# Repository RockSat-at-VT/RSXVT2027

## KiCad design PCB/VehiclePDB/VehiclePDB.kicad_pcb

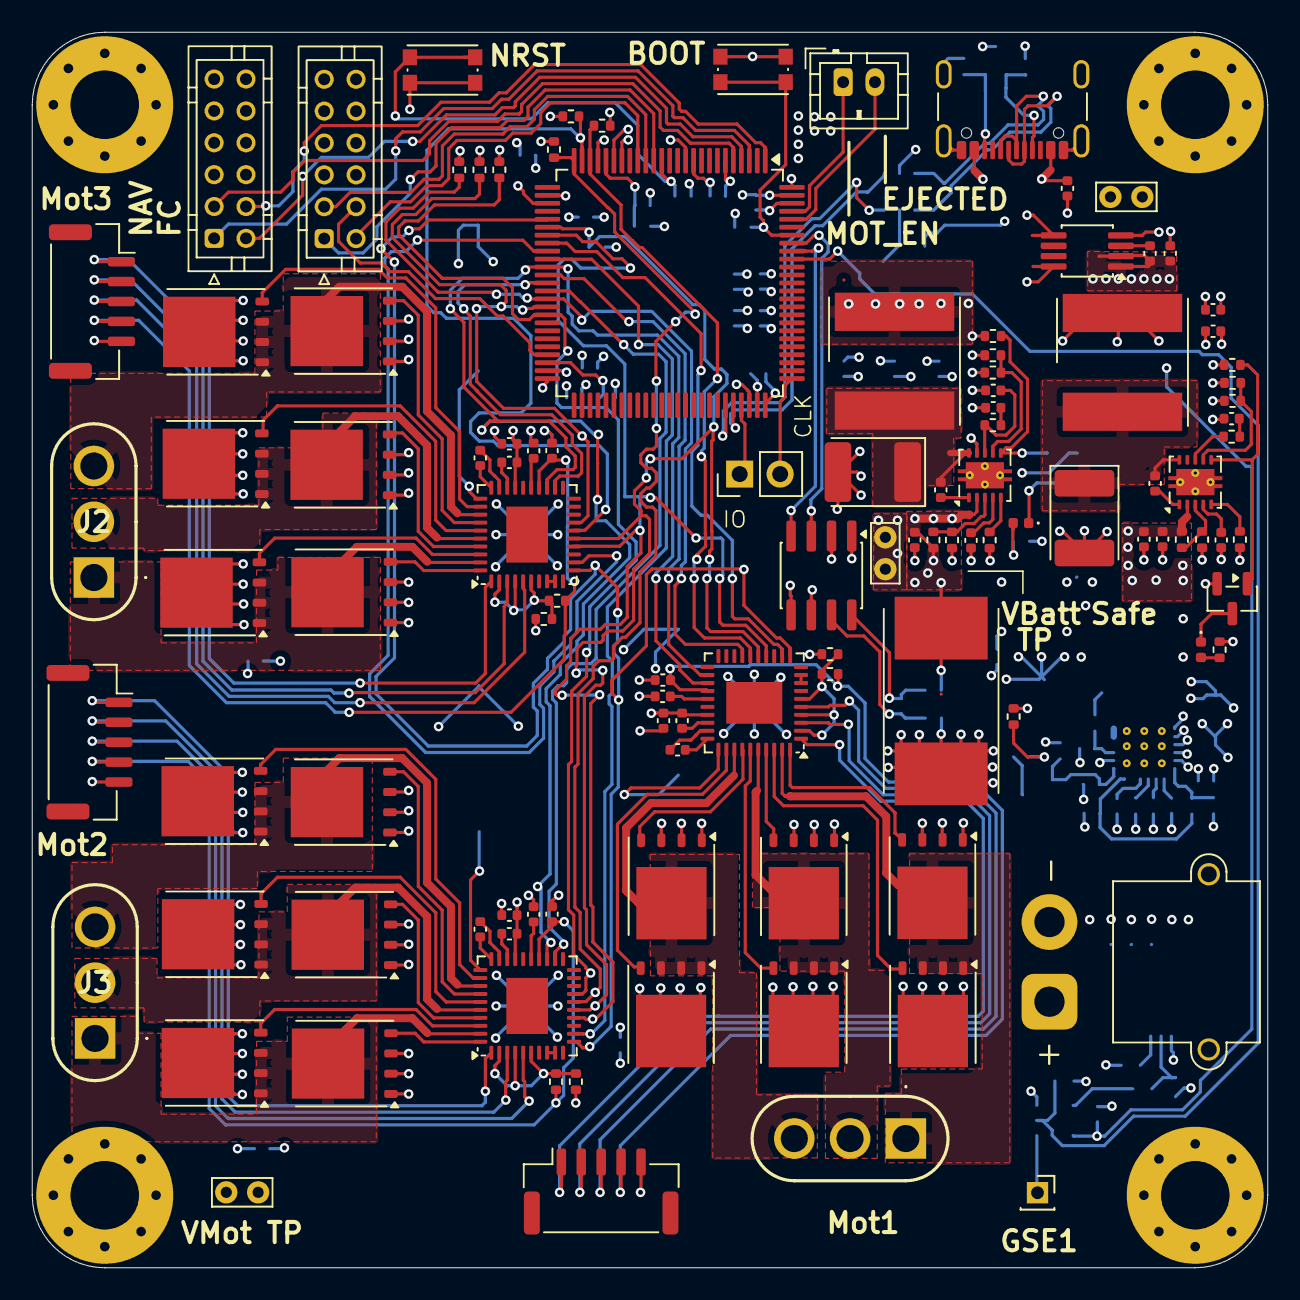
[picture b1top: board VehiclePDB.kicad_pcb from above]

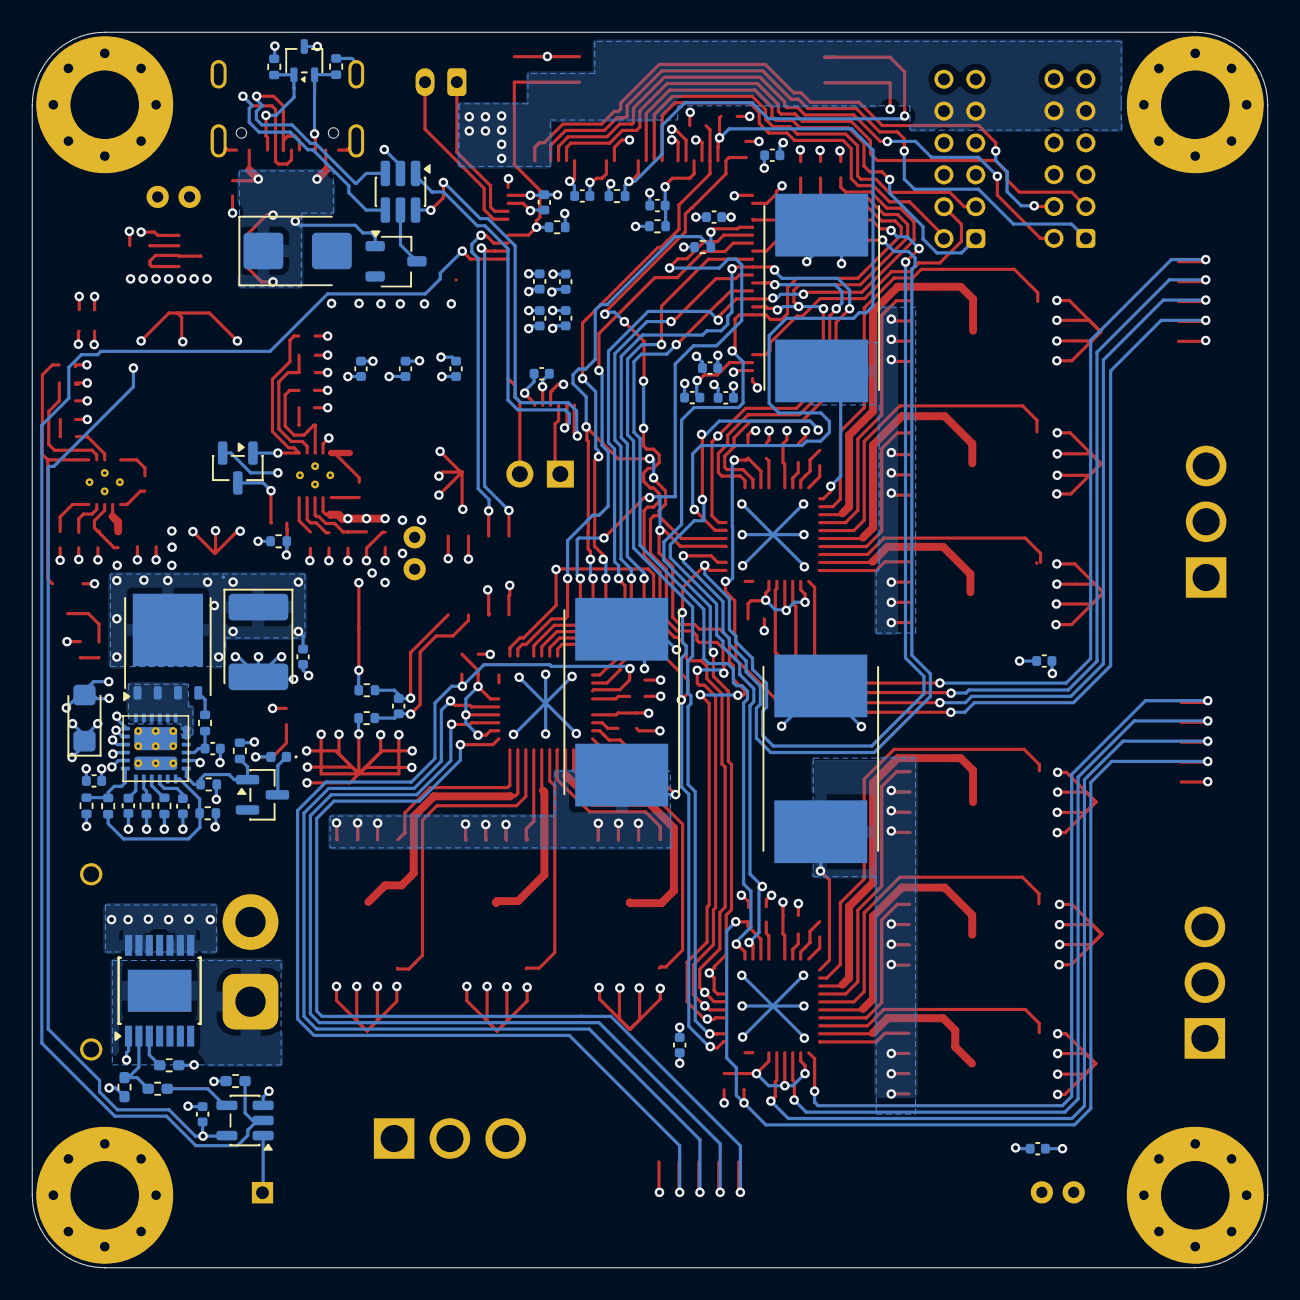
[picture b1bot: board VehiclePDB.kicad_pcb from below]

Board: 4 copper layers, 77.6 x 77.5 mm, 173 parts (63 on the bottom side), 151 nets.

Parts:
C1: 6.8p; C_0402_1005Metric
C2, C3, C16: 100u; C_0402_1005Metric
C4, C6, C32: .01u; C_0402_1005Metric
C5: 4.7n; C_0402_1005Metric
C7, C23, C25, C31, C35, C41, C45, C53, C57: 1u; C_0402_1005Metric
C8: 2.2n; C_0402_1005Metric
C9: 4.3n; C_0402_1005Metric
C10: 8.2n; C_0402_1005Metric
C11: 400u; C_0402_1005Metric
C12: 6.8u; C_0402_1005Metric
C13: 1.2n; C_0402_1005Metric
C14, C15, C28, C29: 2.2u; C_0402_1005Metric
C17, C33: 10u; C_0402_1005Metric
C18, C21, C22, C24, C26, C40, C43, C44, C52, C55, C56: .1u; C_0402_1005Metric
C19, C20: 47u; C_0402_1005Metric
C27, C42, C54: 470u; C_0402_1005Metric
C30, C34, C36, C37, C38, C39, C46, C47, C48, C50: 100n; C_0402_1005Metric
C49: 4.7u; C_0402_1005Metric
D1, D2, D4: SD2114S040S8R0; D_2114_3652Metric
D3, D6, D7: LED; LED_0402_1005Metric
D5: SMF15A; D_SMF
D10: SMBJ6.0A-E3/52; D_SMB
D11: BAT54; TSOT-23
J2, J3: Bullet Conector; MR30PBFB
J4: Conn_01x02_Pin; PinHeader_1x02_P2.54mm_Vertical
J5: USB_C_Receptacle_USB2.0_14P; USB_C_Receptacle_GCT_USB4105-xx-A_16P_TopMnt_Horizontal
J6: Hall1; JST_GH_SM05B-GHS-TB_1x05-1MP_P1.25mm_Horizontal
J7: Hall2; JST_GH_SM05B-GHS-TB_1x05-1MP_P1.25mm_Horizontal
J8: Hall3; JST_GH_SM05B-GHS-TB_1x05-1MP_P1.25mm_Horizontal
J9: battery connector; AMASS_XT30PW-M_1x02_P2.50mm_Horizontal
J10, J11: Conn_02x06_Odd_Even; JST_PHD_B12B-PHDSS_2x06_P2.00mm_Vertical
J12: Conn_01x01_Socket; PinSocket_1x01_P2.00mm_Vertical
J13: Conn_01x02_Pin; JST_PH_B2B-PH-K_1x02_P2.00mm_Vertical
L1: 15u; L_Wurth_WE-LQS-8040
L2: 10u; L_Wurth_WE-LQS-8040
Mot1: Bullet Conector; MR30PBFB
Q1, Q6, Q7, Q8, Q9, Q10, Q11, Q12, Q13, Q14, Q15, Q16, Q17, Q18, Q19, Q20, Q21, Q22: BSC052N08NS5; TDSON-8-1
Q5: BSC026N08NS5; TDSON-8-1
Q23, Q24, Q25: 2N7002; SOT-23
R1, R6: 20k; R_0402_1005Metric
R2, R5, R18, R22, R23, R24, R39, R42, R46: 10k; R_0402_1005Metric
R3: 412k; R_0402_1005Metric
R4: 31.6k; R_0402_1005Metric
R7: 500k; R_0402_1005Metric
R8: 14k; R_0402_1005Metric
R9: 50k; R_0402_1005Metric
R10: 226; R_0402_1005Metric
R11: 5m; R_Shunt_Vishay_WSR2_WSR3
R12: 1.24k; R_0402_1005Metric
R13: 365k; R_0402_1005Metric
R14: 124k; R_0402_1005Metric
R15: 30.1k; R_0402_1005Metric
R16, R19: 105k; R_0402_1005Metric
R17: 15.4k; R_0402_1005Metric
R20, R26, R27, R28, R29, R30, R31, R32, R33, R34, R35, R36, R37, R44: 4.7k; R_0402_1005Metric
R21: 52.3; R_0402_1005Metric
R25, R43, R58: 30m; R_Shunt_Vishay_WSR2_WSR3
R38: 47; R_0402_1005Metric
R40, R41: 5.1k; R_0402_1005Metric
R45: 10k; R_0402_1005Metric_Pad0.72x0.64mm_HandSolder
R47: 2; R_0402_1005Metric
R49, R50, R51: 4.7k; R_0402_1005Metric_Pad0.72x0.64mm_HandSolder
R52, R53: 10; R_0402_1005Metric
SW1, SW2: SW_Push; SW_Push_1P1T_NO_CK_KMR2
TP1, TP1#2, TP2: TestPoint; TestPoint_Bridge_Pitch2.0mm_Drill0.7mm
U1: STM32H523VCTx; LQFP-100_14x14mm_P0.5mm
U2: 74LVC1G32; SOT-23-5
U3, U4: TPS54240DRC; Texas_DRC0010J_ThermalVias
U5, U17, U19: DRV8308; Texas_RHA0040E_VQFN-40-1EP_6x6mm_P0.5mm_EP3.52x2.62mm
U6: TPS25983
U7: BTS7004-1EPP; Infineon_PG-TSDSO-14-22
U9: INA219AxD; SOIC-8_3.9x4.9mm_P1.27mm
U11: IP4234CZ6; SC-74-6_1.55x2.9mm_P0.95mm
U13: TPD2E2U06DCK; SOT-323_SC-70
U14: LT1762-3.3; MSOP-8_3x3mm_P0.65mm

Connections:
3V3: C19.2, C20.2, C30.1, C32.1, C33.1, C34.2, C35.2, C37.1, C38.1, C39.1, C46.1, C47.1, C48.1, C49.1, C50.1, J10.7, J10.8, J11.7, J11.8, J12.1 (Pin_1_1), L2.2, R4.1, R18.2, R28.1, R30.1, R32.1, R34.2, R35.2, R36.2, R37.2, R38.2, R39.1, SW2.1, U1.6 (VBAT), U1.11 (VDD), U1.22 (VDDA), U1.28 (VDD), U1.50 (VDD), U1.73 (VDDUSB), U1.75 (VDD), U1.100 (VDD), U2.1, U2.5 (VCC), U9.5 (VS), U14.1 (OUT), U14.2 (SENSE)
5V: C2.1, C3.1, C16.1, J10.9, J10.10, J11.9, J11.10, L1.2, R21.1, R46.2
/Batt Togle/IS_Ejected: R45.1, U1.91 (PB5), U2.2
/FC2PDB.CLK: J10.4, U1.47 (SPI2_SCK)
/FC2PDB.CS: J10.1, U1.15 (PC0)
/FC2PDB.MISO: J10.2, U1.17 (SPI2_MISO)
/FC2PDB.MOSI: J10.3, U1.16 (SPI2_MOSI)
/Motor Controler MCU/CurrInfo.SCL: U1.92 (I2C1_SCL), U9.4 (SCL)
/Motor Controler MCU/CurrInfo.SDA: U1.93 (I2C1_SDA), U9.3 (SDA)
/Motor Controler MCU/IS_EJECTED: J13.2, U1.96 (PB9)
/Motor Controler MCU/MOTOR_OFF: J13.1, U1.97 (PE0)
/Motor Controler MCU/PDB.CLK: J4.2, U1.76 (DEBUG_JTCK-SWCLK)
/Motor Controler MCU/PDB.IO: J4.1, U1.72 (DEBUG_JTMS-SWDIO)
/Motor Driver One/Motor1.ENABLE: U1.37 (PB2), U5.22 (ENABLE)
/Motor Driver One/Motor1.FAULTn: R37.1, U1.40 (PE9), U5.17 (~FAULTn)
/Motor Driver One/Motor1.FGOUT: R28.2, U1.23 (TIM2_CH1), U5.16 (FGOUT)
/Motor Driver One/Motor1.SPI_CS: U1.33 (PC4), U5.12 (SCS)
/Motor Driver One/Motors_Low: Q6.1 (S), Q6.2 (S), Q6.3 (S), Q7.1 (S), Q7.2 (S), Q7.3 (S), Q9.1 (S), Q9.2 (S), Q9.3 (S), R25.1, U5.31 (ISEN)
/Motor Driver One/U.High: Q1.4 (G), U5.32 (UHSG)
/Motor Driver One/U.Low: Q6.4 (G), U5.34 (ULSG)
/Motor Driver One/U.Switch: Mot1.3, Q1.1 (S), Q1.2 (S), Q1.3 (S), Q6.5 (D), U5.33 (U)
/Motor Driver One/UP: J6.1, U5.1 (UHP)
/Motor Driver One/V.High: Q8.4 (G), U5.35 (VHSG)
/Motor Driver One/V.Low: Q7.4 (G), U5.37 (VLSG)
/Motor Driver One/V.Switch: Mot1.2, Q7.5 (D), Q8.1 (S), Q8.2 (S), Q8.3 (S), U5.36 (V)
/Motor Driver One/VP: J6.2, U5.3 (VHP)
/Motor Driver One/VREG: C24.2, J6.4, R26.1, U5.24 (VREG)
/Motor Driver One/W.High: Q10.4 (G), U5.38 (WHSG)
/Motor Driver One/W.Low: Q9.4 (G), U5.40 (WLSG)
/Motor Driver One/W.Switch: Mot1.1, Q9.5 (D), Q10.1 (S), Q10.2 (S), Q10.3 (S), U5.39 (W)
/Motor Driver One/WP: J6.3, U5.5 (WHP)
/Motor Driver Three/Motor3.ENABLE: U1.39 (PE8), U19.22 (ENABLE)
/Motor Driver Three/Motor3.FAULTn: R35.1, U1.42 (PE11), U19.17 (~FAULTn)
/Motor Driver Three/Motor3.FGOUT: R32.2, U1.25 (TIM2_CH3), U19.16 (FGOUT)
/Motor Driver Three/Motor3.RESET: U1.36 (PB1), U5.23 (RESET), U17.23 (RESET), U19.23 (RESET)
/Motor Driver Three/Motor3.SPI_CLK: U1.30 (SPI1_SCK), U5.11 (SCLK), U17.11 (SCLK), U19.11 (SCLK)
/Motor Driver Three/Motor3.SPI_CS: U1.35 (PB0), U19.12 (SCS)
/Motor Driver Three/Motor3.SPI_MISO: R34.1, U1.31 (SPI1_MISO), U5.15 (SDATAO), U17.15 (SDATAO), U19.15 (SDATAO)
/Motor Driver Three/Motor3.SPI_MOSI: U1.32 (SPI1_MOSI), U5.14 (SDATAI), U17.14 (SDATAI), U19.14 (SDATAI)
/Motor Driver Three/Motors_Low: Q18.1 (S), Q18.2 (S), Q18.3 (S), Q20.1 (S), Q20.2 (S), Q20.3 (S), Q22.1 (S), Q22.2 (S), Q22.3 (S), R58.1, U19.31 (ISEN)
/Motor Driver Three/U.High: Q17.4 (G), U19.32 (UHSG)
/Motor Driver Three/U.Low: Q18.4 (G), U19.34 (ULSG)
/Motor Driver Three/U.Switch: J3.3, Q17.1 (S), Q17.2 (S), Q17.3 (S), Q18.5 (D), U19.33 (U)
/Motor Driver Three/UP: J8.1, U19.1 (UHP)
/Motor Driver Three/V.High: Q19.4 (G), U19.35 (VHSG)
/Motor Driver Three/V.Low: Q20.4 (G), U19.37 (VLSG)
/Motor Driver Three/V.Switch: J3.2, Q19.1 (S), Q19.2 (S), Q19.3 (S), Q20.5 (D), U19.36 (V)
/Motor Driver Three/VP: J8.2, U19.3 (VHP)
/Motor Driver Three/VREG: C56.2, J8.4, R44.1, U19.24 (VREG)
/Motor Driver Three/W.High: Q21.4 (G), U19.38 (WHSG)
/Motor Driver Three/W.Low: Q22.4 (G), U19.40 (WLSG)
/Motor Driver Three/W.Switch: J3.1, Q21.1 (S), Q21.2 (S), Q21.3 (S), Q22.5 (D), U19.39 (W)
/Motor Driver Three/WP: J8.3, U19.5 (WHP)
/Motor Driver Two/Motor2.ENABLE: U1.38 (PE7), U17.22 (ENABLE)
/Motor Driver Two/Motor2.FAULTn: R36.1, U1.41 (PE10), U17.17 (~FAULTn)
/Motor Driver Two/Motor2.FGOUT: R30.2, U1.24 (TIM2_CH2), U17.16 (FGOUT)
/Motor Driver Two/Motor2.SPI_CS: U1.34 (PC5), U17.12 (SCS)
/Motor Driver Two/Motors_Low: Q12.1 (S), Q12.2 (S), Q12.3 (S), Q14.1 (S), Q14.2 (S), Q14.3 (S), Q16.1 (S), Q16.2 (S), Q16.3 (S), R43.1, U17.31 (ISEN)
/Motor Driver Two/U.High: Q11.4 (G), U17.32 (UHSG)
/Motor Driver Two/U.Low: Q12.4 (G), U17.34 (ULSG)
/Motor Driver Two/U.Switch: J2.3, Q11.1 (S), Q11.2 (S), Q11.3 (S), Q12.5 (D), U17.33 (U)
/Motor Driver Two/UP: J7.1, U17.1 (UHP)
/Motor Driver Two/V.High: Q13.4 (G), U17.35 (VHSG)
/Motor Driver Two/V.Low: Q14.4 (G), U17.37 (VLSG)
/Motor Driver Two/V.Switch: J2.2, Q13.1 (S), Q13.2 (S), Q13.3 (S), Q14.5 (D), U17.36 (V)
/Motor Driver Two/VP: J7.2, U17.3 (VHP)
/Motor Driver Two/VREG: C44.2, J7.4, R31.1, U17.24 (VREG)
/Motor Driver Two/W.High: Q15.4 (G), U17.38 (WHSG)
/Motor Driver Two/W.Low: Q16.4 (G), U17.40 (WLSG)
/Motor Driver Two/W.Switch: J2.1, Q15.1 (S), Q15.2 (S), Q15.3 (S), Q16.5 (D), U17.39 (W)
/Motor Driver Two/WP: J7.3, U17.5 (WHP)
/PDB2NAV.CLK: J11.4, U1.1 (SPI4_SCK)
/PDB2NAV.CS: J11.1, U1.3 (PE4)
/PDB2NAV.MISO: J11.2, U1.4 (SPI4_MISO)
/PDB2NAV.MOSI: J11.3, U1.5 (SPI4_MOSI)
/Post Battery Protection/PG: Q23.1 (G), R1.2, R2.1, U6.13 (PG)
/USB Conector/PORT.D+: U1.71 (USB_DP), U11.1
/USB Conector/PORT.D-: U1.70 (USB_DM), U11.6
/USB Conector/PreESD.D+: J5.A6 (D+), J5.B6 (D+), U11.3
/USB Conector/PreESD.D-: J5.A7 (D-), J5.B7 (D-), U11.4
/USB Conector/VBUS_RAW: C31.1, D10.1 (A1), D11.1 (A), J5.A4 (VBUS), J5.A9 (VBUS), J5.B4 (VBUS), J5.B9 (VBUS), U14.5 (~SHDN), U14.8 (IN)
/Vehicle 3v3 Buck/PG: Q24.1 (G), R18.1, U3.6 (PWRGD)
/Vehicle 5V Buck/PG: Q25.1 (G), R46.1, U4.6 (PWRGD)
GND: C1.2, C2.2, C3.2, C4.2, C5.1, C6.2, C8.1, C9.2, C10.2, C11.2, C12.2, C13.1, C14.2, C15.2, C16.2, C17.2, C19.1, C20.1, C24.1, C25.1, C26.2, C27.2, C28.2, C29.2, C30.2, C31.2, C33.2, C34.1, C35.1, C36.2, C37.2, C38.2, C39.2, C42.2, C43.2, C44.1, C45.1, C46.2, C47.2, C48.2, C49.2, C50.2, C54.2, C55.2, C56.1, C57.1, D1.2 (A), D2.2 (A), D4.2 (A), D5.2 (A2), D10.2 (A2), J5.A1 (GND), J5.A12 (GND), J5.B1 (GND), J5.B12 (GND), J5.SH (SHIELD), J6.5, J7.5, J8.5, J9.2, J10.5, J10.6, J10.11, J10.12, J11.5, J11.6, J11.11, J11.12, Q23.2 (S), Q24.2 (S), Q25.2 (S), R2.2, R3.2, R5.2, R9.1, R10.2, R12.2, R13.2, R15.2, R17.2, R22.2, R25.2, R27.2, R29.2, R33.2, R40.2, R41.1, R42.1, R43.2, R45.2, R50.1, R51.1, R58.2, SW1.1, U1.10 (VSS), U1.19 (VSSA), U1.20 (VREF-), U1.27 (VSS), U1.49 (VSS), U1.74 (VSS), U1.99 (VSS), U2.3 (GND), U3.9 (GND), U3.11 (GND), U4.9 (GND), U4.11 (GND), U5.13 (SMODE), U5.19 (CLKIN), U5.20 (BRAKE), U5.21 (DIR), U5.26 (GND), U5.41 (GND), U6.4 (GND), U6.5 (GND), U6.11 (NRETRY), U6.14 (GND), U6.26 (GND), U7.1 (GND), U9.1 (A1), U9.2 (A0), U9.6 (GND), U11.2 (VN), U13.3, U14.4 (GND), U17.13 (SMODE), U17.19 (CLKIN), U17.20 (BRAKE), U17.21 (DIR), U17.26 (GND), U17.41 (GND), U19.13 (SMODE), U19.19 (CLKIN), U19.20 (BRAKE), U19.21 (DIR), U19.26 (GND), U19.41 (GND)
unnamed: C5.2, R6.1
unnamed: C13.2, R19.1
unnamed: C28.1, U1.98 (VCAP)
unnamed: C29.1, U1.48 (VCAP)
unnamed: C18.1, D2.1 (K), L2.1, U3.10 (PH)
unnamed: D3.2 (A), R20.2
unnamed: D3.1 (K), Q23.3 (D)
unnamed: C21.1, D4.1 (K), L1.1, U4.10 (PH)
unnamed: D6.2 (A), R23.1
unnamed: D6.1 (K), Q25.3 (D)
unnamed: D7.2 (A), R24.1
unnamed: D7.1 (K), Q24.3 (D)
unnamed: D11.3 (K), U11.5 (VP)
unnamed: J5.A5 (CC1), R40.1, U13.1
unnamed: J5.B5 (CC2), R41.2, U13.2
unnamed: Q5.4 (G), R47.1
unnamed: Q5.1 (S), Q5.2 (S), Q5.3 (S), U6.17 (OUT), U6.18 (OUT), U6.19 (OUT), U6.20 (OUT), U6.21 (OUT), U6.22 (OUT), U6.23 (OUT), U6.24 (OUT)
unnamed: R49.1, U2.4
unnamed: R42.2, SW2.2, U1.94 (BOOT0)
unnamed: R39.2, SW1.2, U1.14 (NRST)
unnamed: C36.1, R38.1, U1.21 (VREF+)
unnamed: C18.2, U3.1 (BOOT)
unnamed: R6.2, U3.8 (COMP)
unnamed: R14.2, R15.1, U3.3 (EN)
unnamed: R3.1, U3.5 (RT/CLK)
unnamed: C4.1, U3.4 (SS/TR)
unnamed: R4.2, R5.1, U3.7 (VSENSE)
unnamed: C21.2, U4.1 (BOOT)
unnamed: C1.1, R19.2, U4.8 (COMP)
unnamed: R16.2, R17.1, U4.3 (EN)
unnamed: R13.1, U4.5 (RT/CLK)
unnamed: C12.1, U4.4 (SS/TR)
unnamed: R21.2, R22.1, U4.7 (VSENSE)
unnamed: C22.1, U5.30 (CP1)
unnamed: C22.2, U5.29 (CP2)
unnamed: U5.8 (FGFB), U5.9 (FGINN_TACH)
unnamed: R26.2, R27.1, U5.2 (UHN), U5.4 (VHN), U5.6 (WHN)
unnamed: C23.1, U5.28 (VCP)
unnamed: C25.2, U5.25 (VINT)
unnamed: R7.1, R8.2, U6.6 (EN/UVLO)
unnamed: R10.1, U6.8 (ILIM)
unnamed: R12.1, U6.9 (IMON)
unnamed: C9.1, U6.7 (ITIMER)
unnamed: R8.1, R9.2, U6.12 (OVLO)
unnamed: C8.2, U6.10 (RETRY_DEL)
unnamed: C10.1, R47.2, U6.15 (dVdt)
unnamed: R51.2, U7.3 (DEN)
unnamed: R49.2, R50.2, U7.2 (IN)
unnamed: C7.1, R52.2, U9.8 (IN+)
unnamed: C7.2, R53.2, U9.7 (IN-)
unnamed: C32.2, U14.3 (BYP)
unnamed: C40.1, U17.30 (CP1)
unnamed: C40.2, U17.29 (CP2)
unnamed: U17.8 (FGFB), U17.9 (FGINN_TACH)
unnamed: R29.1, R31.2, U17.2 (UHN), U17.4 (VHN), U17.6 (WHN)
unnamed: C41.1, U17.28 (VCP)
unnamed: C45.2, U17.25 (VINT)
unnamed: C52.1, U19.30 (CP1)
unnamed: C52.2, U19.29 (CP2)
unnamed: U19.8 (FGFB), U19.9 (FGINN_TACH)
unnamed: R33.1, R44.2, U19.2 (UHN), U19.4 (VHN), U19.6 (WHN)
unnamed: C53.1, U19.28 (VCP)
unnamed: C57.2, U19.25 (VINT)
VBatt: C6.1, D5.1 (A1), R7.2, U6.1 (IN), U6.2 (IN), U6.3 (IN), U6.16 (IN), U6.25 (IN), U7.8 (OUT), U7.9 (OUT), U7.10 (OUT), U7.12 (OUT), U7.13 (OUT), U7.14 (OUT)
VBattRaw: J9.1, U7.15 (VS)
VBattSafe: C11.1, C14.1, C15.1, C17.1, D1.1 (K), Q5.5 (D), R1.1, R11.1, R14.1, R16.1, R20.1, R23.2, R24.2, R52.1, TP1#2.1 (1_1), U3.2 (VIN), U4.2 (VIN)
VMot: C23.2, C26.1, C27.1, C41.2, C42.1, C43.1, C53.2, C54.1, C55.1, Q1.5 (D), Q8.5 (D), Q10.5 (D), Q11.5 (D), Q13.5 (D), Q15.5 (D), Q17.5 (D), Q19.5 (D), Q21.5 (D), R11.2, R53.1, TP2.1 (1_1), U5.27 (VM), U17.27 (VM), U19.27 (VM)
